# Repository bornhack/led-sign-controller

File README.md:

# LED Sign controller

## Firmware

[Rust firmware](https://github.com/Orange-Murker/bornhack_led_matrix)

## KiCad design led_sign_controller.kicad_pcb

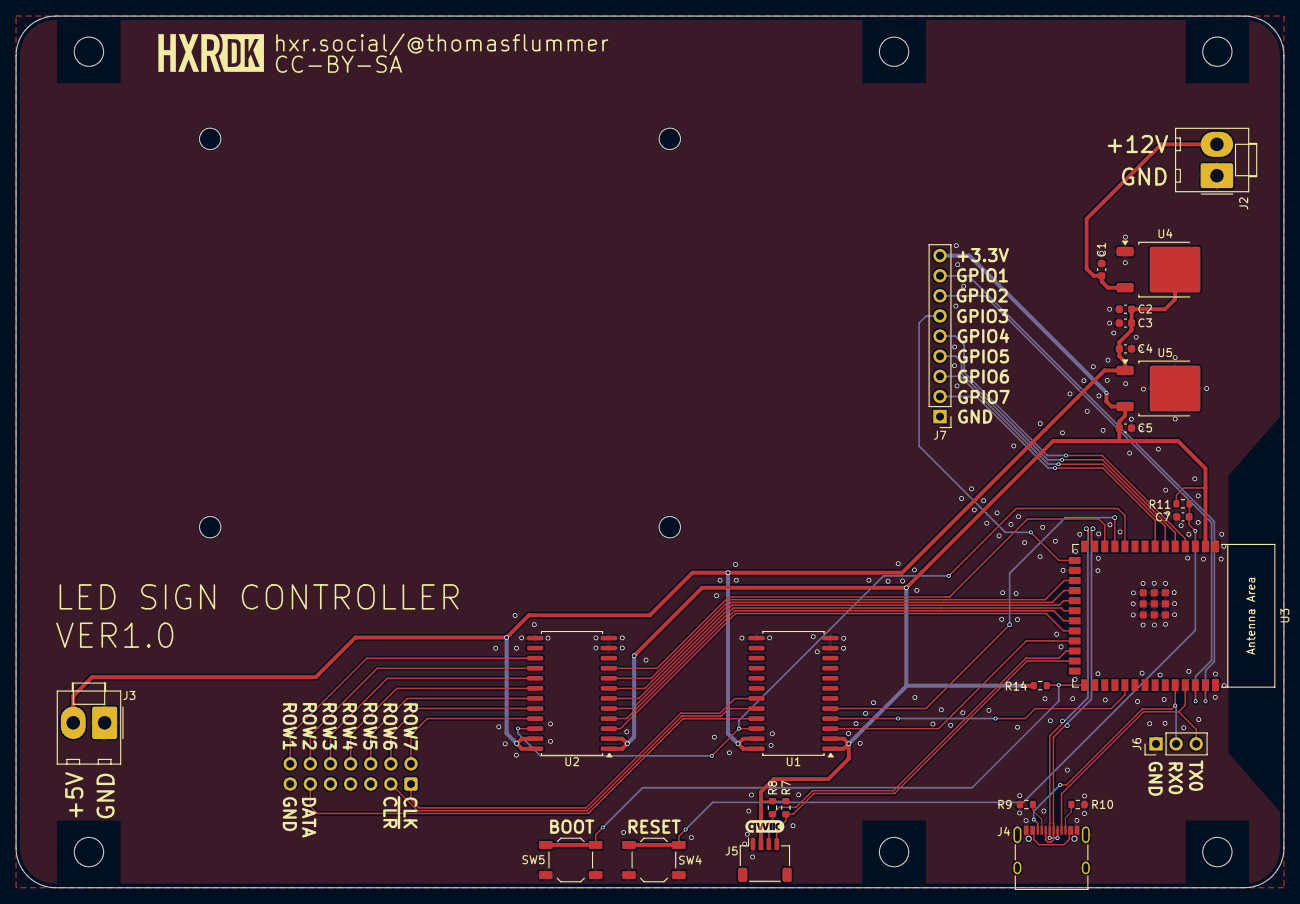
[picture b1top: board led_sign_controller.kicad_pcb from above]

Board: 2 copper layers, 160.0 x 110.0 mm, 26 parts (1 on the bottom side), 43 nets.

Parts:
C1, C2, C3, C4, C5: 10uF; C_0603_1608Metric
C7: 1uF; C_0603_1608Metric
J1: Conn_02x07_Odd_Even; IDC-Header_2x07_P2.54mm_Vertical
J2, J3: Conn_01x02_Pin; Molex_KK-396_A-41791-0002_1x02_P3.96mm_Vertical
J4: USB_C_Receptacle_USB2.0_16P; USB_C_Receptacle_XKB_U262-16XN-4BVC11
J5: Qwiic; JST_SH_SM04B-SRSS-TB_1x04-1MP_P1.00mm_Horizontal
J6: Conn_01x03_Pin; PinHeader_1x03_P2.54mm_Vertical
J7: Conn_01x09_Pin; PinHeader_1x09_P2.54mm_Vertical
R7, R8: 10k; R_0603_1608Metric
R9, R10: 5.1K; R_0603_1608Metric
R11, R14: 10K; R_0603_1608Metric
SW4: RESET; SW_SPST_TL3342
SW5: BOOT; SW_SPST_TL3342
U1, U2: SN74LVC8T245; SOIC-24W_7.5x15.4mm_P1.27mm
U3: ESP32-S3-WROOM-1
U4: AZ1117-5.0; TO-252-2
U5: AP7363-33D-13; TO-252-2

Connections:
+3.3V: C5.1, J5.2, J7.9, R7.1, R8.1, R11.1, R14.1, U1.1 (V_{CCA}), U1.2 (DIR), U2.1 (V_{CCA}), U2.2 (DIR), U3.2 (3V3), U5.3 (VO)
+5V: C2.1, C3.1, C4.1, J3.2, U1.23 (V_{CCB}), U1.24 (V_{CCB}), U2.23 (V_{CCB}), U2.24 (V_{CCB}), U4.2 (VO), U5.1 (VI)
+12V: C1.1, J2.2, U4.3 (VI)
/ESP32-S3 with USB-C/COLUMN_CLK: U1.5 (A3), U3.11 (GPIO18/U1RXD/ADC2_CH7/CLK_OUT3)
/ESP32-S3 with USB-C/COLUMN_SER: U1.3 (A1), U3.23 (GPIO21)
/ESP32-S3 with USB-C/COLUMN_~CLR: U1.4 (A2), U3.31 (GPIO38/FSPIWP/SUBSPIWP)
/ESP32-S3 with USB-C/GPIO1: J7.8, U3.39 (GPIO1/TOUCH1/ADC1_CH0)
/ESP32-S3 with USB-C/GPIO2: J7.7, U3.38 (GPIO2/TOUCH2/ADC1_CH1)
/ESP32-S3 with USB-C/GPIO3: J7.6, U3.15 (GPIO3/TOUCH3/ADC1_CH2)
/ESP32-S3 with USB-C/GPIO4: J7.5, U3.4 (GPIO4/TOUCH4/ADC1_CH3)
/ESP32-S3 with USB-C/GPIO5: J7.4, U3.5 (GPIO5/TOUCH5/ADC1_CH4)
/ESP32-S3 with USB-C/GPIO6: J7.3, U3.6 (GPIO6/TOUCH6/ADC1_CH5)
/ESP32-S3 with USB-C/GPIO7: J7.2, U3.7 (GPIO7/TOUCH7/ADC1_CH6)
/ESP32-S3 with USB-C/OUTPUT_ENABLE: U1.22 (~OE), U2.22 (~OE), U3.10 (GPIO17/U1TXD/ADC2_CH6)
/ESP32-S3 with USB-C/ROW_1: U2.9 (A7), U3.12 (GPIO8/TOUCH8/ADC1_CH7/SUBSPICS1)
/ESP32-S3 with USB-C/ROW_2: U2.8 (A6), U3.17 (GPIO9/TOUCH9/ADC1_CH8/FSPIHD/SUBSPIHD)
/ESP32-S3 with USB-C/ROW_3: U2.7 (A5), U3.18 (GPIO10/TOUCH10/ADC1_CH9/FSPICS0/FSPIIO4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)
/ESP32-S3 with USB-C/ROW_4: U2.6 (A4), U3.19 (GPIO11/TOUCH11/ADC2_CH0/FSPID/FSPIIO5/S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)
/ESP32-S3 with USB-C/ROW_5: U2.5 (A3), U3.20 (GPIO12/TOUCH12/ADC2_CH1/FSPICLK/FSPIIO6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)
/ESP32-S3 with USB-C/ROW_6: U2.4 (A2), U3.21 (GPIO13/TOUCH13/ADC2_CH2/FSPIQ/FSPIIO7/S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)
/ESP32-S3 with USB-C/ROW_7: U2.3 (A1), U3.22 (GPIO14/TOUCH14/ADC2_CH3/FSPIWP/FSPIDQS/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)
/ESP32-S3 with USB-C/RX0: J4.B8 (SBU2), J6.2, U3.36 (U0RXD/GPIO44/CLK_OUT2)
/ESP32-S3 with USB-C/SCL: J5.4, R7.2, U3.25 (GPIO48/SPICLK_N/SUBSPICLK_N_DIFF)
/ESP32-S3 with USB-C/SDA: J5.3, R8.2, U3.24 (GPIO47/SPICLK_P/SUBSPICLK_P_DIFF)
/ESP32-S3 with USB-C/TX0: J4.A8 (SBU1), J6.3, U3.37 (U0TXD/GPIO43/CLK_OUT1)
/ESP32-S3 with USB-C/USB_BUS_POWER: J4.A4 (VBUS), J4.A9 (VBUS), J4.B4 (VBUS), J4.B9 (VBUS)
/ESP32-S3 with USB-C/USB_D+: J4.A6 (D+), J4.B6 (D+), U3.14 (GPIO20/U1CTS/ADC2_CH9/CLK_OUT1/USB_D+)
/ESP32-S3 with USB-C/USB_D-: J4.A7 (D-), J4.B7 (D-), U3.13 (GPIO19/U1RTS/ADC2_CH8/CLK_OUT2/USB_D-)
COLUMN_CLK_OUT: J1.1, U1.19 (B3)
COLUMN_SER_OUT: J1.11, U1.21 (B1)
COLUMN_~CLR_OUT: J1.3, U1.20 (B2)
GND: C1.2, C2.2, C3.2, C4.2, C5.2, C7.2, J1.13, J2.1, J3.1, J4.A1 (GND), J4.A12 (GND), J4.B1 (GND), J4.B12 (GND), J4.S1 (SHIELD), J5.1, J6.1, J7.1, R9.2, R10.2, SW4.1, SW5.2, U1.11 (GND), U1.12 (GND), U1.13 (GND), U2.11 (GND), U2.12 (GND), U2.13 (GND), U3.1 (GND), U3.16 (GPIO46), U3.40 (GND), U3.41 (GND), U4.1 (GND), U5.2 (GND)
unnamed: J4.A5 (CC1), R9.1
unnamed: J4.B5 (CC2), R10.1
unnamed: C7.1, R11.2, SW4.2, U3.3 (EN)
unnamed: R14.2, SW5.1, U3.27 (GPIO0/BOOT)
ROW_1_OUT: J1.14, U2.15 (B7)
ROW_2_OUT: J1.12, U2.16 (B6)
ROW_3_OUT: J1.10, U2.17 (B5)
ROW_4_OUT: J1.8, U2.18 (B4)
ROW_5_OUT: J1.6, U2.19 (B3)
ROW_6_OUT: J1.4, U2.20 (B2)
ROW_7_OUT: J1.2, U2.21 (B1)

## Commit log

2025-07-25 Added link to firmware
2025-07-25 Image added

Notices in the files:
led_sign_controller.kicad_pcb:
CC-BY-SA
